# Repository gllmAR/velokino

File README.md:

veloKino
========

VeloKino est une recherche-création axée sur la réinjection cinétique en interactivité.

Issues de variations autour des vélos stationnaires interactifs,  Vélokino explore le registre expressif entre un effort fourni et une réponse audiovisuelle. 

Spécifiquement appliquée au mouvement de rotation cyclique, Vélokino à pour objectif  d'être une installation interactive autoalimentée et intégrée au contexte urbain.

Par son usage,  l'installation cherche à suggérer une réflexion sur la consommation électrique individuelle et collective grandissante à l'ère du numérique.

Ce projet s'inscrit dans le cadre d'une maitrise en Média expérimental à l'UQAM réalisé par Guillaume Arseneault et débuté à l'automne 2013.

## objectifs 
* Créer un dispositif qui transforme l'effort du mouvement en réponse audiovisuelle
*  Transformer l'énergie produite en phénomènes audio lumineux
* Développer une expérience individuelle et collective 

## intentions 

VéloKino est une installation interactive alimentée par l’effort de l’interacteur.  VéloKino utilise une série de roue chacun couplés à une dynamo,  un condensateur,  une diode électroluminescente,  un haut-parleur et un microprocesseur.  Cet amalgame génére des compositions uniques lorsqu’un ou des utilisateurs sollicite l’installation.

VéloKino ce veut une oeuvre qui inspire le changement d’un rapport de consommation avec l’énergie nécessaire pour nous divertir.  VeloKino s'inscrit dans le média povera et est fortement influencée par des oeuvres comme *agit POV* 
Cette création s’articule autour de l’effort à fournir par le ou les participants pour alimenter lumières, haut-parleurs et électronique de contrôle.
Le tout,  dans l’objectif de créer un support audiovisuel, interactif autoalimenté et intégré au contexte urbain qui suggère par son utilisation une réflexion sur la consommation électrique individuelle et collective.

## Thématique

VéloKino explore la thématique de la dépendance énergétique en établissant une corrélation entre l’effort à fournir pour illuminer et émettre des sons. 
Ce projet se veut une critique  de l’industrie du divertissement qui requiert un déploiement toujours de plus en plus important en terme d’énergie, de ressources matériel et de déchets technologique. 
 
En ce sens, VéloKino combat l’obsolescence en utilisant un matériel volontairement simple. Bien que limité, VéloKino cherche à exprimer un registre maximum d’expression à travers le minimalisme de la technologie qu’il utilise. VéloKinos questionne en ce sens la notion de «Mur» technologique en fixant le support dans une dynamique d’évolution de la programmation et non par le remplacement du matériel.  

## Genre

VéloKino est une étude sur l'interactivité qui explore les relations d’expression entre un témoin lumineux,  un haut-parleur, un microprocesseur et une source d’énergie fournie par un interacteur. 
C’est une installation extérieure urbaine autoalimentée  qui peut s’intègrer à un support déjà existant, soit les bornes de vélo-libre-service.  Chaque unité stationnaire révéle un comportement unique autonome qui s’harmonise, lorsqu’utilisé par plusieurs.  

## Traitement esthétique

Dispositif :  
 
* Intégrer le dispositif de la manière la plus transparente possible tout en ayant une réflexion adéquate quant à la résistance du matériel aux intempéries, aux vandalismes et aux vols.  
* Utiliser des bornes existantes en effectuant que très peu de changement à leur fonctionnement.  La borne doit demeurer utilisable en tout temps.
* Favoriser le soulèvement de la roue arrière dans l’optique d’une intégration transparente et portable 
* Favoriser l’utilisation de technologie verte peu couteuse,  durable et remplaçable en cas de bris.
* permettre aux vélos non-Bixi  de participer également
* intégrer un chargeur de téléphone pour maximiser l’utilisation transversale du dispositif

Interaction et interactivité:

* Établir une corrélation évolutive entre l’effort fourni et une réponse audio lumineuse. 
* Vectoriser une dynamique lorsque plusieurs utilisateurs utilisent le dispositif en même temps.
* Programmer une personnalité unique pour chacune des unités de VéloKino. (réponse audiolumineuse)
Sonore : - Le spectre sonore sera volontairement limité au registre du microprocesseur soit très près de l’esthétique «chiptune».
* Lumière : - Explorer l’expression potentielle d’un unique pixel unique disposant de contrôle sur l’intensité du rouge du vert et du bleu.  

## originalité

Bien que plusieurs installations utilisant des vélos stationnaires ont déjà eu lieu à travers le monde et même à Montréal, l’équation entre intégration dans l’espace public,  portabilité et expression artistique reste à explorer.  C’est le traitement unique de chacun des dispositifs,  son alimentation autonome et son design portable et ancrable qui constitue les clef de voute de ce projet.  Ce dispositif se veut mobile, reproductible et adaptable à différents contextes de diffusion.  

## aspect expérimental

Aller chercher un maximum de registre d’expression à travers un minimum de composante soit un haut-parleur,  un microprocesseur à très faible consommation électrique et une diode électroluminescente RGB. Développer des technologies d’alimentation électrique telle que le moteur-roue,  optimiser les performances électriques en utilisant des super-condensateurs, trouver un moyen éco responsable d’assurer la gestion du courant. 

## diffusion

* Une collaboration avec l’organisme Bixi est à planifier.
* une diffusion de type furtive serait à tester en processus d’expérimentation
* une diffusion en collaboration avec le partenariat du Quartier des spectacles est à envisager.  Je n’écarte pas la possibilité de coupler le système comme interface de contrôle pour un système de projection architecturale.
* Le projet est exportable dans toutes les villes du monde disposant d’un service de vélo libre-service (Paris,  Bruxelle,  Toronto, Londres, etc. )

## incertitudes 

* Obtention des interfaces Bixi : faillite potentielle de Bixi,  collaboration de leur part nécessaire.  
* Similitudes avec le projet : CHAMP DE PIXELS au parc Émilie-gamelin 2010  
* Installation du dispositif en ville : Collaboration nécessaire du PQDS  
* Indestructibilité relative du matériel et du design :  installation urbaine au centre-ville
* cout de matériaux
* Recherche et développement technologique étendu

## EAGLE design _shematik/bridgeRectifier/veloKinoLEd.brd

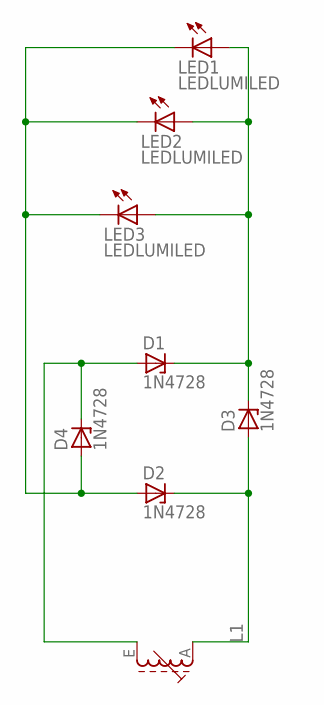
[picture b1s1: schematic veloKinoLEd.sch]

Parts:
D1, D2, D3, D4: 1N4728; DO41Z10
L1: 71E
LED1, LED2, LED3: LEDLUMILED; LUMILED

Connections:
unnamed: D1.C, D3.C, LED1.2+ (A), LED2.2+ (A), LED3.2+ (A)
unnamed: D2.C, D3.A, L1.A
unnamed: D2.A, D4.A, LED1.4- (C), LED2.4- (C), LED3.4- (C)
unnamed: D1.A, D4.C, L1.E

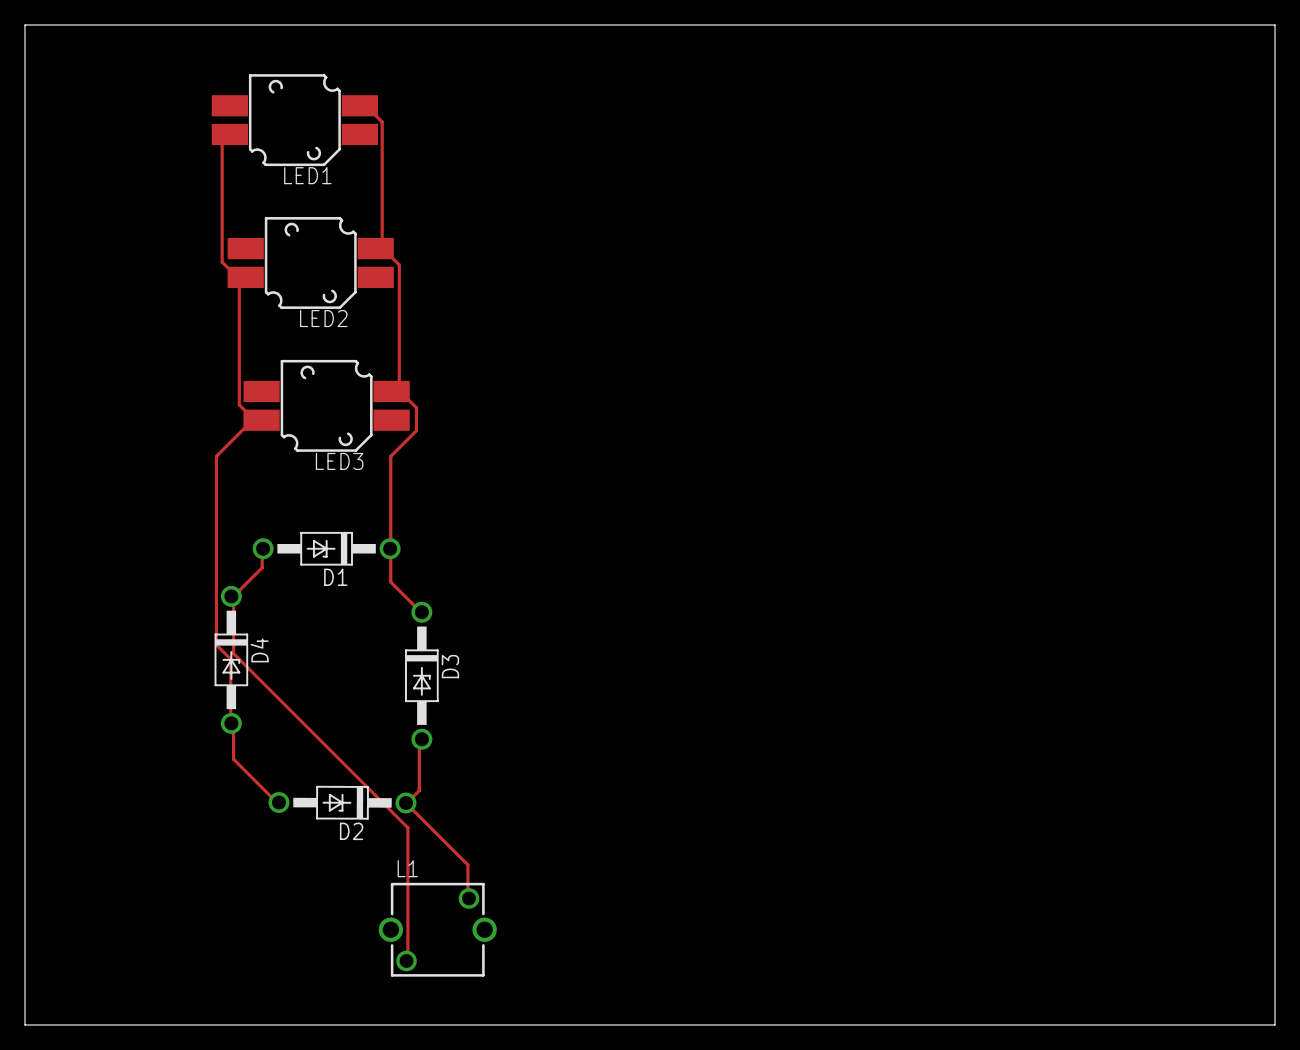
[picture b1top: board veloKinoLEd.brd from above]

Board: 2 copper layers, 100.0 x 80.0 mm, 8 parts (0 on the bottom side), 4 nets.

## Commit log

2014-06-22 Transition de tumblr Vers GitHub
    Journal de bord du projet vélo kino de tumblr Vers github
2014-06-22 Changements et correction
    après premier commit, correction des erreurs
2014-06-22 update le lien pdf vers raw
2014-06-23 Restructuration Nomemclature
    Section : académique, blog, projets
2014-06-23 ajout direction électrique
    electrodynamo Commit
2014-06-23 intégration des intentions
    Modification du readme
2014-06-23 Create gh-pages branch via GitHub
2014-06-24 Rename 0000_dev_change_log.md to README.md
2014-06-24 Ajustement MrPEach
    Fixer une erreur de permission…
2014-06-27 TestCompatibilité
2014-06-27 get Get
2014-06-27 changement à la description du projet
    tester en même temps le merge vers gh-pages
2014-06-27 config yml edit
2014-06-27 # markdown: kramdown dans config
2014-06-27 retour au depart de config
2014-06-27 add markdown
2014-06-27 retrait des accent dans la description de config
2014-06-27 des test
2014-06-27 d'autre teste
2014-06-27 asdf
2014-06-27 changement de nom
2014-06-27 nom qui bug
2014-06-27 changement au url
2014-06-27 edit de la config
2014-06-27 bio de Guillaume
2014-06-27 update sur blogpost
2014-06-27 re test
2014-06-27 rajout du div
2014-06-27 update de blogpost
2014-06-27 encore
2014-06-27 un autre test
2014-06-27 nom et espace
2014-06-27 autre espace patente
2014-06-27 update des blog post
2014-06-27 ajustement dossier
2014-06-27 changement de nom et test
2014-06-27 rer re
2014-06-27 fu le blog
2014-06-27 la path absolue est le secret!
    http://raw.githubusercontent.com/gllmAR/velokino/gh-pages/_posts/assets/
2014-06-27 majuscule
2014-06-27 update sur le lien pdf
2014-06-27 modif de contenu
    merge
2014-06-27 Changement au niveau de l'arborescence
    Transition vers __veloKino au lieu de projet
    sert à simplifier et clarifier le github
2014-06-27 fav icon et layout
2014-06-27 ajustement
2014-06-28 ajout et motif electrodynamo
2014-06-30 Ajout de deux post.
    algo et contactless dynamo
2014-07-01 tester le master
2014-07-05 reconfiguration de l'arbre
2014-08-06 Recherche et développement sur le bridge rectifier
2014-08-06 retour au inputPullUpOSC pour le cone
    ajout de documentation et autre choses diverses
2014-08-07 Commit de la mort à 5 am!!!
2014-09-24 update sur SyphoneFullsScreen
2014-11-24 nouvelleBranche de projet veloKino
2014-11-26 update pour yonder
    v1
2014-11-26 update le nom du serial pour raspberry pi
2014-11-26 reupdate du marcel pour le serial
2014-11-26 reupdate du serial
2014-11-27 changer pour un mix mono spécifique à l'install
2015-05-01 update arbol
2015-05-05 update début prog et documentation
2015-05-05 link sur l'image dans le readme
2015-05-07 ajout d'un projet jonquiere
2015-05-07 correction coquilles jonquiere
2015-05-08 update documentation
2015-05-08 reupdate documentation
2015-05-22 commit de la dev Brulante
2015-05-23 ajout photo connectique
2015-09-08 correction et ajout majeur
